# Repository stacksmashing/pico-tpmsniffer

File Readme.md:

# Pico TPMSniffer

> This is experimental software and hardware. It's not ready to use for professional or production use.

The board (in /hardware/) is compatible with the "Debug Card" connector found on some Lenovo laptops only for LPC. 

The firmare supports LPC and SPI TPMs. Where for the later sniffing is performed on the BIOS Chip (typically Winbond 25Qxxx) SPI lines are shared with the TPM Chip.

! The hardware is currently not compatible with the SPI / SPI-BIOS ! Currently you need to use either a 
testclip, probe pins, solder to the pins or other means to connect to the  TPM / BIOS pins sniffing SPI.

## Building

```
export PICO_SDK_PATH=path to your Pico-SDK
mkdir build
cd build
cmake ..
make
```

## Hardware

The board files are in `hardware/`, the Pogo pins used are of the type: P50-B1-16mm

## Usage

### LPC

Just connect to the serial port, boot your machine, and push against the card connector!

### SPI / SPI-BIOS

Connect (BIOS Chip) DI, DO, CLK, SELECT and GND according to this 
* GPIO 2 -----> DI
* GPIO 3 -----> DO
* GPIO 4 -----> CLK
* GPIO 5 -----> SELECT
* GND Pico ---> GND Bios/Tpm

Start the laptop before the 5seconds countdown is finished. Otherwise the sniffer might not capture
the TPM key. The sniffer still seems to have an issue with the first 1 second of the boot sequence.

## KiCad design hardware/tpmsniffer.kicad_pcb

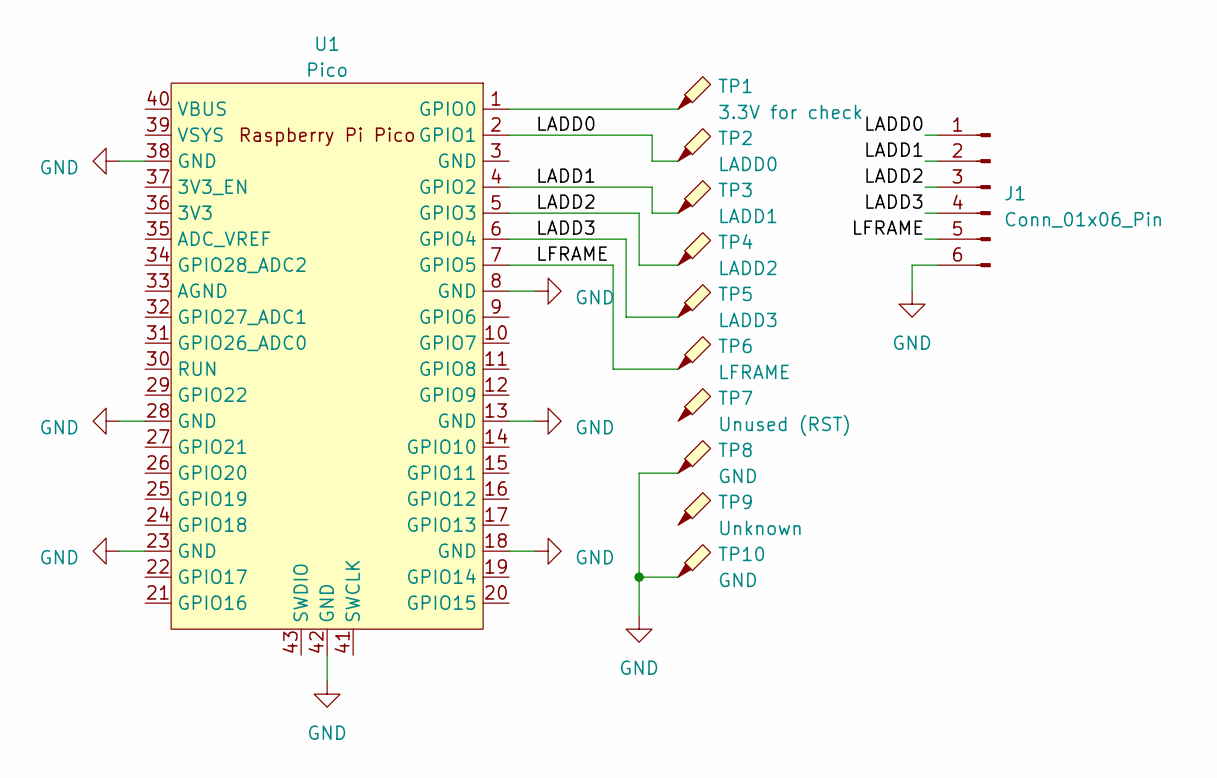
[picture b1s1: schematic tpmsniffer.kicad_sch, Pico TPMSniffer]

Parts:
J1: Conn_01x06_Pin; PinSocket_1x06_P2.54mm_Vertical
TP1: 3.3V for check; pogo-p50-b1
TP2: LADD0; pogo-p50-b1
TP3: LADD1; pogo-p50-b1
TP4: LADD2; pogo-p50-b1
TP5: LADD3; pogo-p50-b1
TP6: LFRAME; pogo-p50-b1
TP7: Unused (RST); pogo-p50-b1
TP8, TP10: GND; pogo-p50-b1
TP9: Unknown; pogo-p50-b1
U1: Pico; RPi_Pico_SMD_TH

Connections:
/LADD0: J1.1, TP2.1, U1.2 (GPIO1)
/LADD1: J1.2, TP3.1, U1.4 (GPIO2)
/LADD2: J1.3, TP4.1, U1.5 (GPIO3)
/LADD3: J1.4, TP5.1, U1.6 (GPIO4)
/LFRAME: J1.5, TP6.1, U1.7 (GPIO5)
GND: J1.6, TP8.1, TP10.1, U1.8 (GND), U1.13 (GND), U1.18 (GND), U1.23 (GND), U1.28 (GND), U1.38 (GND), U1.42 (GND)
unnamed: TP1.1, U1.1 (GPIO0)

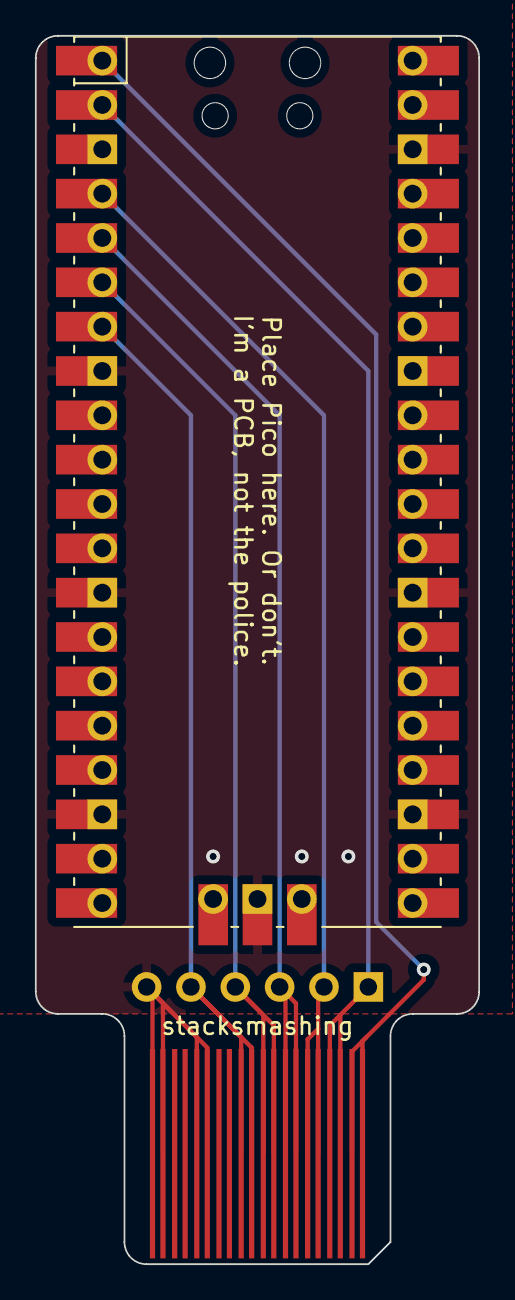
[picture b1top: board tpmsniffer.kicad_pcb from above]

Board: 2 copper layers, 25.4 x 70.4 mm, 12 parts (1 on the bottom side), 7 nets.

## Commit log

2024-02-03 Initial public release
2024-02-11 Update main.c
    Added a wait loop to only start with banner and sniffer once someonce connects to the serial port.
    Also added blinking led, once the pico detects a USB serial connection as additional indicator that things are working.
2024-02-11 Update main.c
    ChatGPT version of trying to take variable VMK headers into concideration.
    The header can actually look like this:
    2c000[0-6]000[1-9]000[0-1]000[0-5]200000
    I am not a programmer, would be cool if you could evaluate if this is okay or not.
    Or if there is maybe even a more sexy way to do it.
2024-03-03 patch to add spi protocol sniffing
2024-03-03 removed build folder
2024-03-03 removed main-spi.c
2024-03-03 comment on protocol select in main()
2024-03-06 spi sniffer update / bug fix
2024-03-06 postpone direct spi sniffing on tpm
2024-03-06 more generec VMK header check
2024-03-10 added capability to sniff SPI communication on the bios chip, added hw select option for either lpc or spi sniffing
2024-03-22 incorporated the latest spi updates into the joint repo
